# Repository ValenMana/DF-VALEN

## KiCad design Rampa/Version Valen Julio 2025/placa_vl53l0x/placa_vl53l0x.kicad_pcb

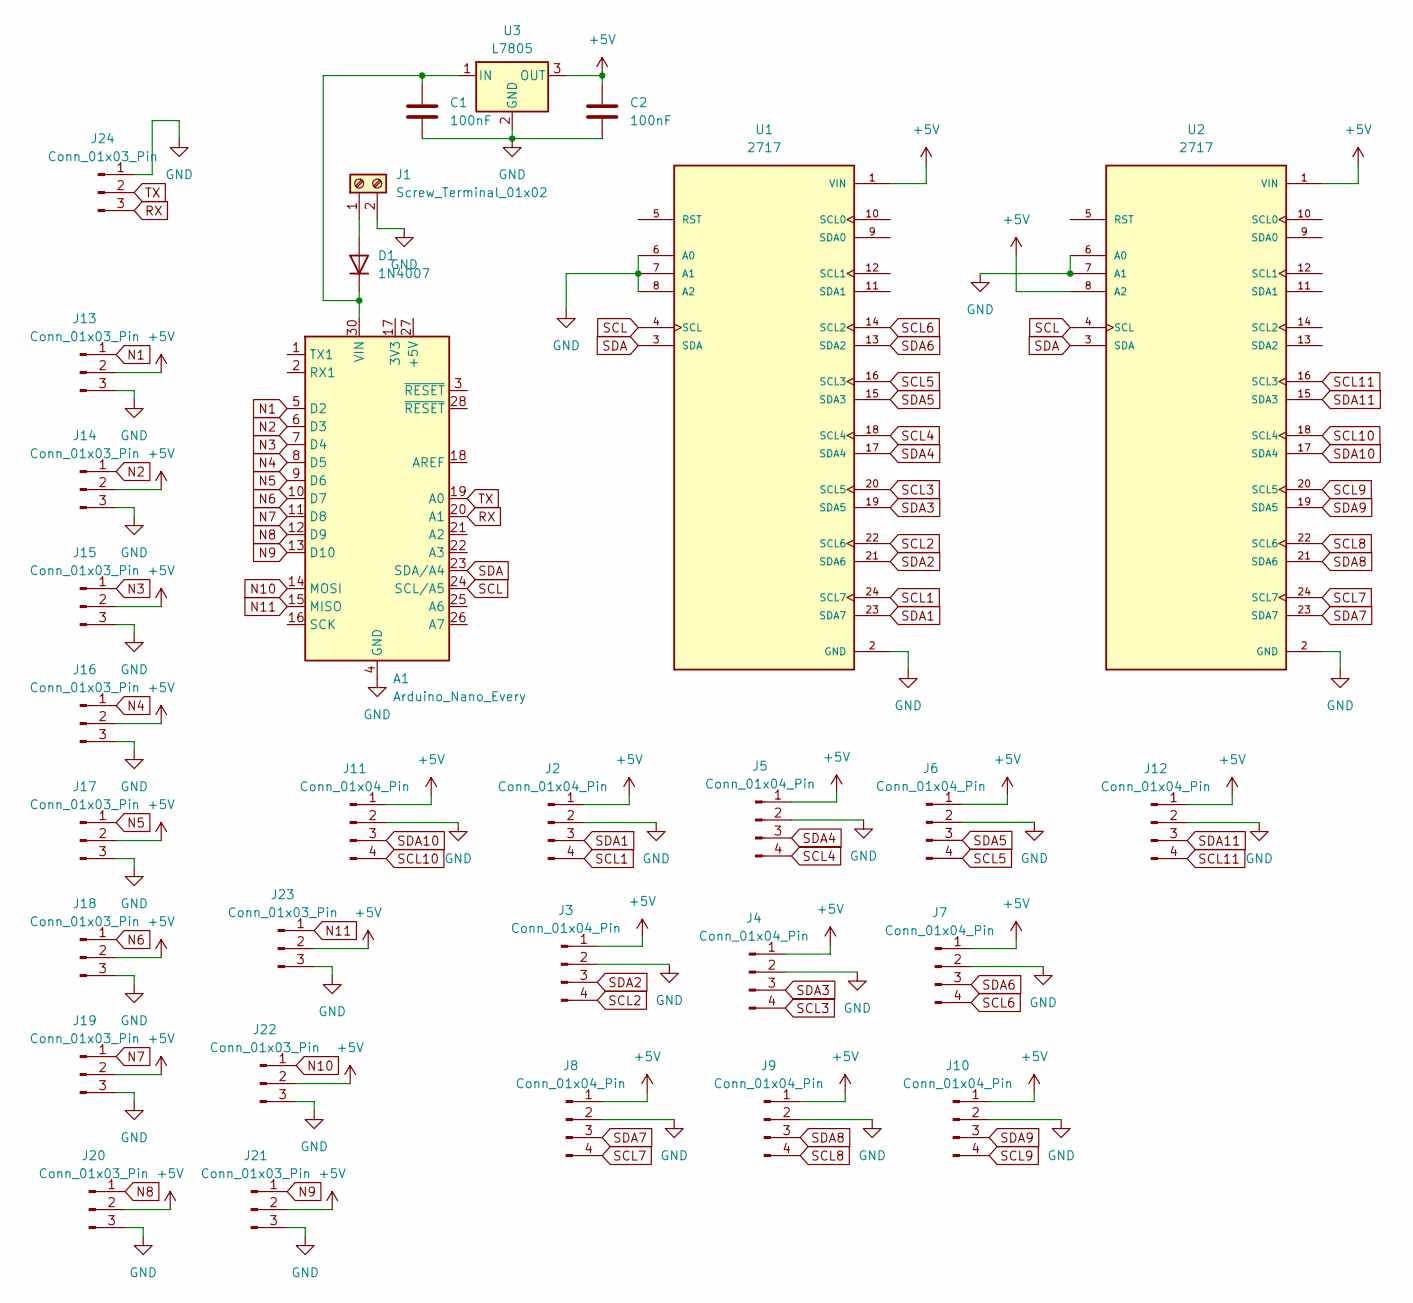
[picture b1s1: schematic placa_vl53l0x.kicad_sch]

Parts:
A1: Arduino_Nano_Every; Arduino_Nano
C1, C2: 100nF; C_Disc_D6.0mm_W2.5mm_P5.00mm
D1: 1N4007; D_DO-41_SOD81_P10.16mm_Horizontal
J1: Screw_Terminal_01x02; TerminalBlock_MetzConnect_Type101_RT01602HBWC_1x02_P5.08mm_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
J2, J3, J4, J5, J6, J7, J8, J9, J10, J11, J12: Conn_01x04_Pin; PinHeader_1x04_P2.54mm_Vertical
J13, J14, J15, J16, J17, J18, J19, J20, J21, J22, J23, J24: Conn_01x03_Pin; PinSocket_1x03_P2.54mm_Vertical_LED
U1, U2: 2717; MODULE_2717; PARTREV Sep 11, 2015
U3: L7805; TO-220-3_Vertical

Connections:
+5V: C2.1, J2.1, J3.1, J4.1, J5.1, J6.1, J7.1, J8.1, J9.1, J10.1, J11.1, J12.1, J13.2, J14.2, J15.2, J16.2, J17.2, J18.2, J19.2, J20.2, J21.2, J22.2, J23.2, U1.1 (VIN), U2.1 (VIN), U2.8 (A2), U3.3 (OUT)
GND: A1.4 (GND), A1.29 (GND), C1.2, C2.2, J1.2, J2.2, J3.2, J4.2, J5.2, J6.2, J7.2, J8.2, J9.2, J10.2, J11.2, J12.2, J13.3, J14.3, J15.3, J16.3, J17.3, J18.3, J19.3, J20.3, J21.3, J22.3, J23.3, J24.1, U1.2 (GND), U1.6 (A0), U1.7 (A1), U1.8 (A2), U2.2 (GND), U2.6 (A0), U2.7 (A1), U3.2 (GND)
N1: A1.5 (D2), J13.1
N2: A1.6 (D3), J14.1
N3: A1.7 (D4), J15.1
N4: A1.8 (D5), J16.1
N5: A1.9 (D6), J17.1
N6: A1.10 (D7), J18.1
N7: A1.11 (D8), J19.1
N8: A1.12 (D9), J20.1
N9: A1.13 (D10), J21.1
N10: A1.14 (MOSI), J22.1
N11: A1.15 (MISO), J23.1
unnamed: A1.30 (VIN), C1.1, D1.1 (K), U3.1 (IN)
unnamed: D1.2 (A), J1.1
RX: A1.20 (A1), J24.3
SCL: A1.24 (SCL/A5), U1.4 (SCL), U2.4 (SCL)
SCL1: J2.4, U1.24 (SCL7)
SCL2: J3.4, U1.22 (SCL6)
SCL3: J4.4, U1.20 (SCL5)
SCL4: J5.4, U1.18 (SCL4)
SCL5: J6.4, U1.16 (SCL3)
SCL6: J7.4, U1.14 (SCL2)
SCL7: J8.4, U2.24 (SCL7)
SCL8: J9.4, U2.22 (SCL6)
SCL9: J10.4, U2.20 (SCL5)
SCL10: J11.4, U2.18 (SCL4)
SCL11: J12.4, U2.16 (SCL3)
SDA: A1.23 (SDA/A4), U1.3 (SDA), U2.3 (SDA)
SDA1: J2.3, U1.23 (SDA7)
SDA2: J3.3, U1.21 (SDA6)
SDA3: J4.3, U1.19 (SDA5)
SDA4: J5.3, U1.17 (SDA4)
SDA5: J6.3, U1.15 (SDA3)
SDA6: J7.3, U1.13 (SDA2)
SDA7: J8.3, U2.23 (SDA7)
SDA8: J9.3, U2.21 (SDA6)
SDA9: J10.3, U2.19 (SDA5)
SDA10: J11.3, U2.17 (SDA4)
SDA11: J12.3, U2.15 (SDA3)
TX: A1.19 (A0), J24.2

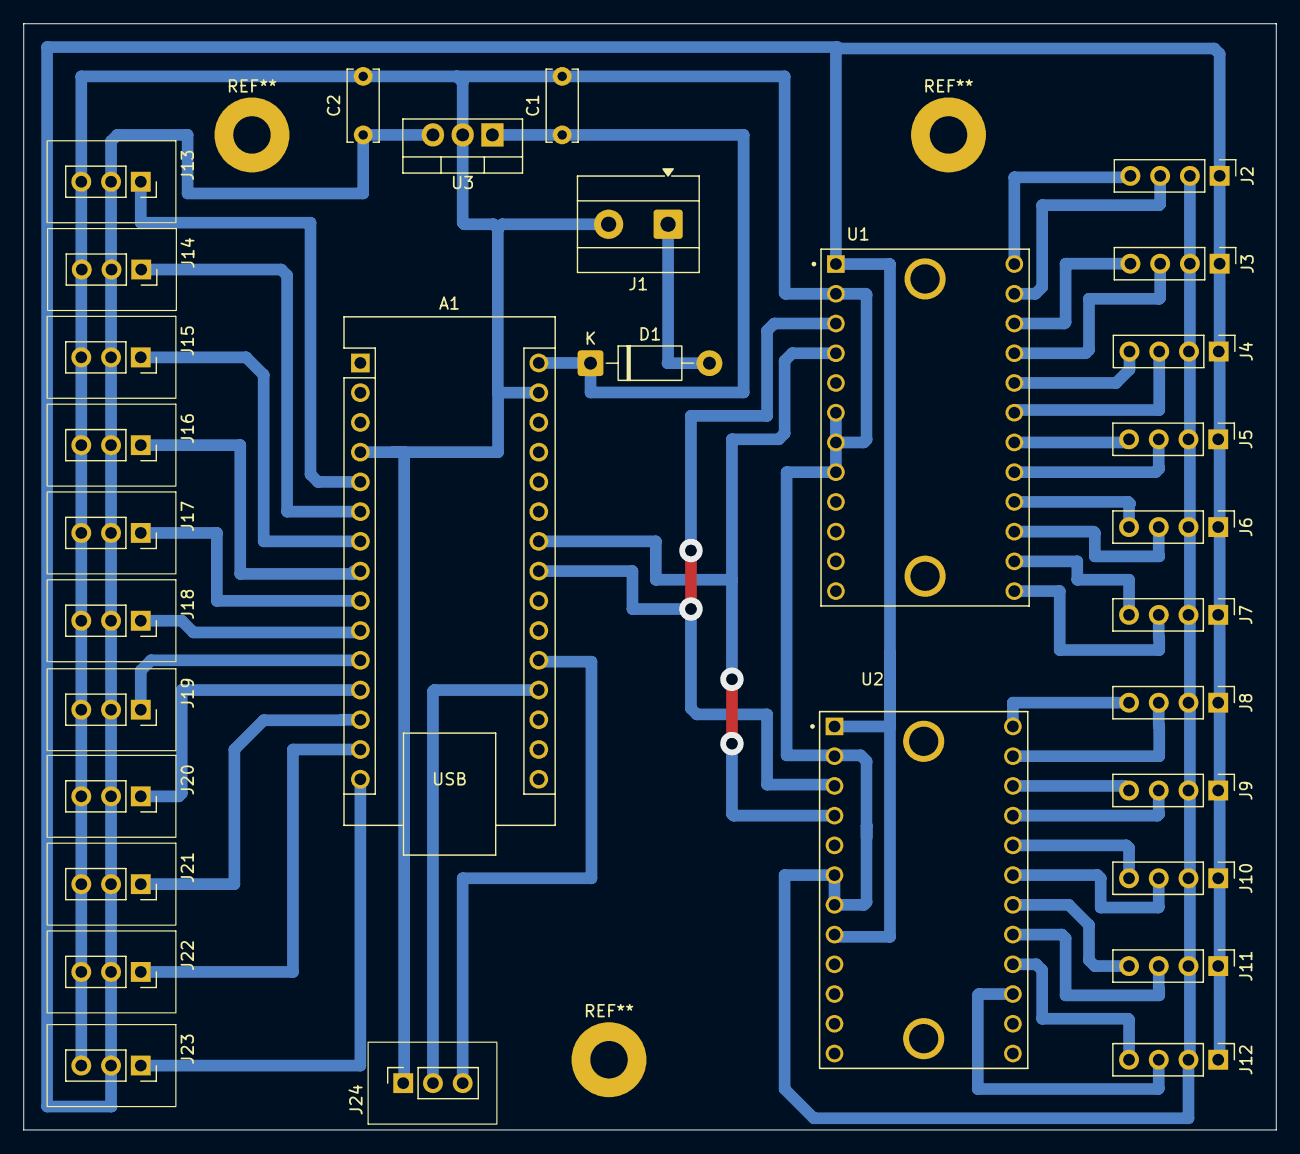
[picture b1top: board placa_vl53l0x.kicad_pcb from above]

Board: 2 copper layers, 107.0 x 94.5 mm, 31 parts (0 on the bottom side), 41 nets.

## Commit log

2025-08-07 Creacion de git ValenMana 07/08/25
2025-08-07 arreglo potencia pelotazo
2025-08-08 comunicacion entre totem y juego via i2c funcionando
2025-08-12 Modificacion de aros a comm i2c (falla pantalla)
2025-08-12 Prueba Raspi
2025-08-12 lo mismo pero de raspi
2025-08-12 totem i2c con Wire1
2025-08-12 comunicacion SPI bidireccional
2025-08-12 master spi bidireccional
2025-08-12 aros con spi sin probar
2025-08-12 aro maso spi
2025-08-12 totem aros spi maso
2025-08-14 Aros v4 sin funcionar
2025-08-14 versiones aros
2025-08-14 pruebas aros
2025-08-14 juego aros falta puntaje
2025-08-14 totem aros sin puntaje
2025-08-18 TOTEM Aros recibiendo puntaje
2025-08-18 Juego Aros enviando puntaje
2025-08-19 Juego Aros funciondo MOSFET 19/8
2025-08-21 No se
2025-08-22 totem neopixel
2025-08-22 totem neo
2025-08-27 Potencia pelotazo, modificado la lectura del sensor y sensibilidad
2025-08-27 octogono modificado, el siguiente no vuelve a ser el mismo
2025-09-02 create DF-183
2025-09-02 DF-183 y ConnectTest
2025-09-02 DF-183
2025-09-02 DF-183 con markdown
2025-09-03 DF-185
2025-09-04 pelotazo timeout
2025-10-31 juegos 31_10
2025-11-10 conos mirko
2026-01-26 reaccion - salto
2026-03-27 final compu vieja
2026-03-27 Anulado sensor 2 aros, zigzag pasadas utlimo y anteultimo mismo pin
2026-03-30 octogono file habilitaciones
